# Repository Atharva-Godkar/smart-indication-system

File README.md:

# Smart Indication System

The aim of the project was to develop a turn indication system for 2 wheelers that will automatically give signals based on position of steering wheel.  This will reduce the miss communication between bike riders & also improve  visibility of vehicle on road during night time. In short it will reduce  accidents. I also made a webpage that helps to monitor the activities of  cyclist and do live location tracking. This will help in immediate medical  assitance to the victim incase of an accident.

## Highlights of the Project

| Tool        | Description |
| ----------- | ----------- |
|  | to program microcontroller like ESP8266 |
|  | used to design PCB for project      |
|  | used to create circuit diagrams |
|  | updates a part of webpage without refreshing it |
|  | used to update the data coming on webpage |
|  | for customization of tables & buttons |
| | for making table, meter tag & button |
|  | for desinging the READMD.md file of github |

## My Webpage

## Live Location Tracking

## Jacket fitted with LED matrix

| Jacket | Breaks Applied | Right Turn |
| ------ | -------------- | ---------- |
|  |  |  |

## Working of Project
Please press the video icon given below to play the video.

## Referrences

 - [Kris Kasprzak](https://rb.gy/9xxxm)
 - [IoT Design](https://rb.gy/anubd)
 - [IoT Design](https://rb.gy/40xbd)
 - [techiesms](https://rb.gy/0wapi)

## Team Members
- [@vansh](https://github.com/VanshD40)
- [@chaudhari]()
- [@ratan]()
- [@godkar](https://github.com/Atharva-Godkar)

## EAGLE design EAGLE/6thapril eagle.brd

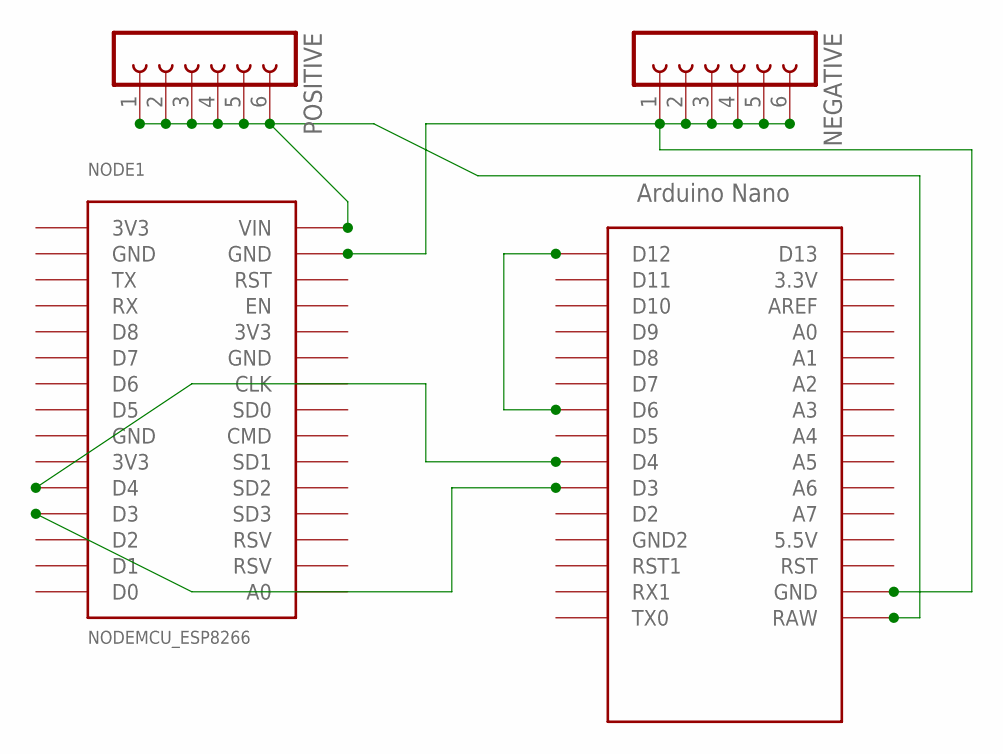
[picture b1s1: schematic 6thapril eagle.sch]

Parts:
NEGATIVE: FE06-1; FE06
NODE1: NODEMCU_ESP8266
POSITIVE: FE06-1; FE06
U$1: NANO

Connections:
3V3: NODE1.3V3@1 (3V3), NODE1.3V3@2 (3V3), NODE1.3V3@3 (3V3)
GND: NODE1.GND@1 (GND), NODE1.GND@2 (GND), NODE1.GND@3 (GND)
unnamed: NODE1.D3, U$1.D3
unnamed: NODE1.D4, U$1.D4
unnamed: NODE1.VIN, POSITIVE.1, POSITIVE.2, POSITIVE.3, POSITIVE.4, POSITIVE.5, POSITIVE.6, U$1.RAW
unnamed: NEGATIVE.1, NEGATIVE.2, NEGATIVE.3, NEGATIVE.4, NEGATIVE.5, NEGATIVE.6, NODE1.GND@4 (GND), U$1.GND
unnamed: U$1.D6, U$1.D12

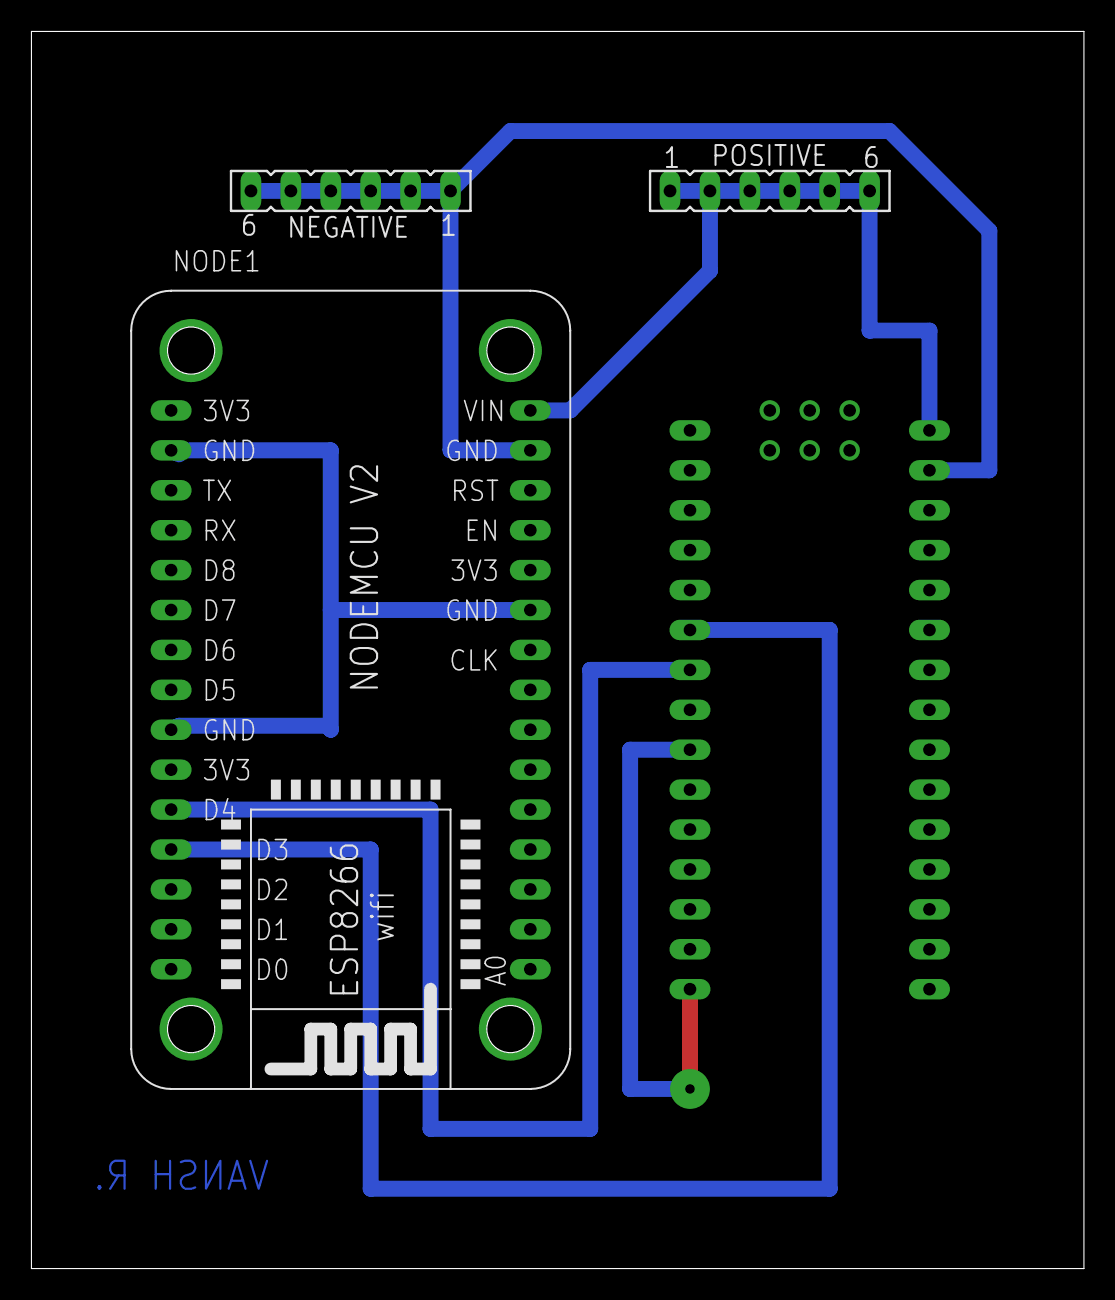
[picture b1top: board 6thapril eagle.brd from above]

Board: 2 copper layers, 67.0 x 78.7 mm, 4 parts (0 on the bottom side), 7 nets.

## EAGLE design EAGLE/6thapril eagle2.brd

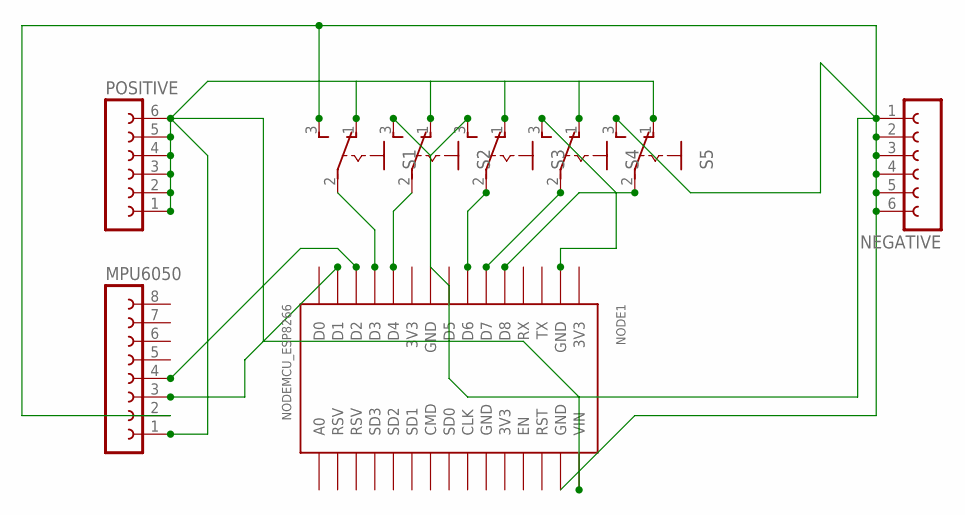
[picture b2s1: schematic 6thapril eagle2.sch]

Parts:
MPU6050: FE08-1; FE08
NEGATIVE: FE06-1; FE06
NODE1: NODEMCU_ESP8266
POSITIVE: FE06-1; FE06
S1, S2, S3, S4, S5: 255SB

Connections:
3V3: NODE1.3V3@1 (3V3), NODE1.3V3@2 (3V3), NODE1.3V3@3 (3V3)
GND: NODE1.GND@3 (GND)
unnamed: NODE1.D3, S1.2
unnamed: NODE1.D4, S2.2
unnamed: NODE1.D6, S3.2
unnamed: NODE1.D7, S4.2
unnamed: NODE1.D8, S5.2
unnamed: MPU6050.2, NEGATIVE.1, NEGATIVE.2, NEGATIVE.3, NEGATIVE.4, NEGATIVE.5, NEGATIVE.6, NODE1.GND@2 (GND), NODE1.GND@4 (GND), S1.3 (S), S2.3 (S), S3.3 (S), S5.3 (S)
unnamed: MPU6050.1, NODE1.VIN, POSITIVE.1, POSITIVE.2, POSITIVE.3, POSITIVE.4, POSITIVE.5, POSITIVE.6, S1.1 (O), S2.1 (O), S3.1 (O), S4.1 (O), S5.1 (O)
unnamed: NODE1.GND@1 (GND), S4.3 (S)
unnamed: MPU6050.3, NODE1.D1
unnamed: MPU6050.4, NODE1.D2

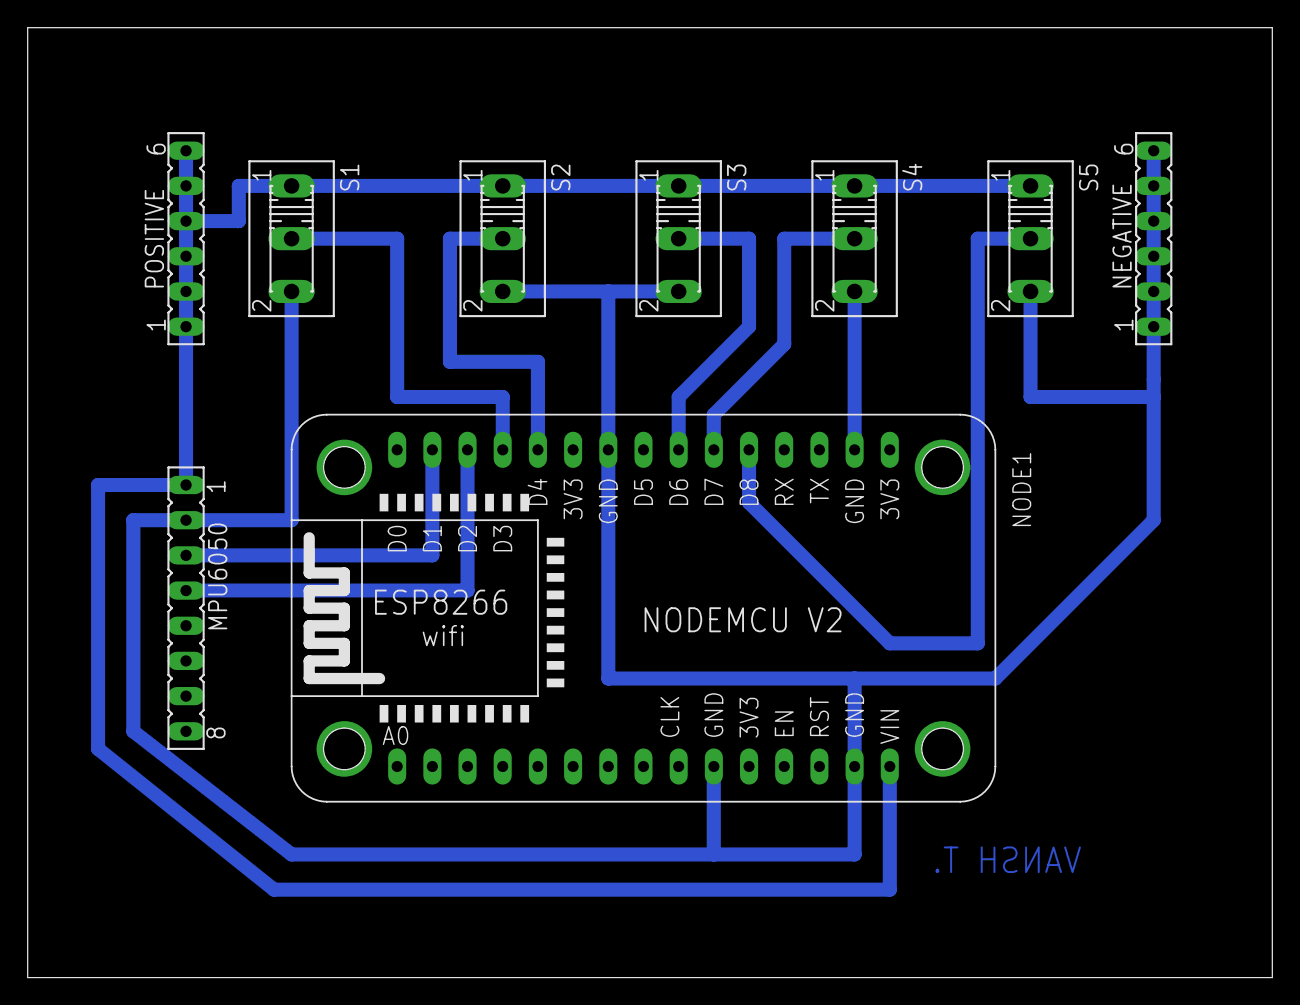
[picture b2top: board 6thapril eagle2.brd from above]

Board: 2 copper layers, 89.8 x 68.6 mm, 9 parts (0 on the bottom side), 11 nets.

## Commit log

2023-06-11 second commit
2023-06-11 third commit
2025-06-14 fourth commit
